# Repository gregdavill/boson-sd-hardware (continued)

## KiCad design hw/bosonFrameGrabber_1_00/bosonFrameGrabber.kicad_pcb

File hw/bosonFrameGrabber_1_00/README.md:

# bosonFrameGrabber v1.00

	Board Status: Discarded
	Note: bad footprint for HyperRam.

A Small FPGA based board. Designed to connect to a FLIR Boson Camera, and save images from the camera to a microSD card.

## Hardware

* ICE40HX8K in csBGA132 package
* HyperRAM: high density, but low pin count.
* QSPI Memory
* MicroSD socket
* MEMs Oscillator
* JST GH SM06 locking Data/Power connector
* JTAG exposed via pogo pin pads.
* 2x 5V tolerant I/Os on connector
* 1x LED!

Prototype Limitations:
* Not quite enough decoupling, not too close to BGA pads.
* 3.3V only! (Integrated LDOs handle FPGA rails, but input power is connected directly to the Boson)
* Non-ideal BGA footprint to reduce prototyping costs.

## Goals

I have not worked with FPGAs in a project before, This project is a toy project of mine, to learn while having a clear goal. 

* Use Icestorm toolchain to develop for FPGA
* Deploy a risc-V softcore into the HX8K.
* Develop a HyperRAM interface.
* Develop/Integrate SDMMC IP. (Intially SD in SPI mode)
* Save Images from the CMOS camera interface to the SD card.

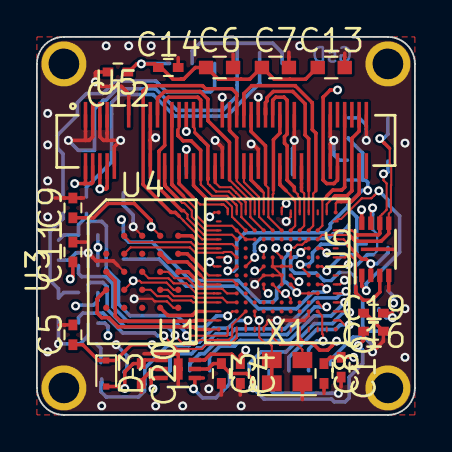
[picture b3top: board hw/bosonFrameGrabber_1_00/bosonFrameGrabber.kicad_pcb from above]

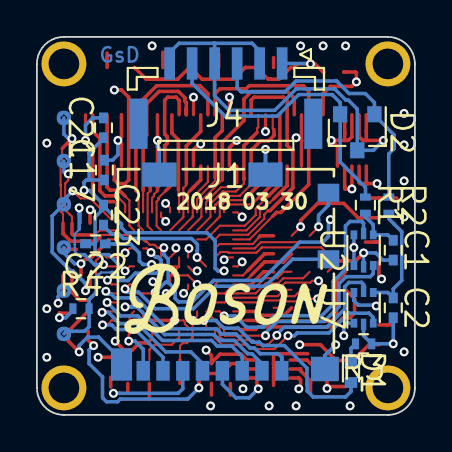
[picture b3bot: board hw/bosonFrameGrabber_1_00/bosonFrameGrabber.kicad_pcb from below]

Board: 4 copper layers, 21.0 x 21.0 mm, 38 parts (16 on the bottom side), 68 nets.

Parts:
C1, C2: 100pF; C_0402
C3, C4: 1uF; C_0402
C5: 100nF; C_0402
C6, C7, C13: 10uF; C_0603
C8, C9, C10, C11, C12, C14, C16, C17, C19, C20, C21, C22, C23: 100n; C_0402
D1: LED; LED_0402
D2: D_TVS_x2_AAC; SOT-23
D3: D_ALT; D_SC-80
J1: JST GH Series; JST_GH_BM06B-GHS-TBT_06x1.25mm_Straight
J4: MicroSD; 1040310811
R1, R2: 100R; R_0402
R3: R; R_0402
R4: 10k; R_0402
U1: MIC5370; DFN-6-1EP_2x2mm_Pitch0.5mm
U2, U7: SN74LVC1T45; SOT-666
U3: ICE40HX8K; csBGA_132
U4: S27KS0641; BGA_24
U5: Boson; DF40_80Pin
U6: AT25SF081; DFN-8-1EP_3x2mm_Pitch0.5mm
X1: ASDMB; Oscillator_SMD_SeikoEpson_SG210-4pin_2.5x2.0mm

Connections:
16MHZ_IN: U3.G1, X1.3
+1V2: C3.1, C17.1, C19.1, C21.1, C22.2, C23.1, U1.5, U3.C8, U3.F8, U3.G6, U3.H9, U3.J4, U3.J7, U3.M8
+1V8: C4.1, C8.1, C9.1, C10.1, C11.1, U1.6, U3.A8, U3.F6, U3.F9, U3.H14, U4.B4, U4.D1, U4.E4
+2V5: C5.1, D3.1, U3.A14
+3V3: C6.1, C7.1, C12.1, C13.1, C14.1, C16.1, C20.1, D3.2, J1.1, J4.4, R4.1, U1.1, U1.3, U1.4, U2.1, U2.6, U3.E3, U3.J6, U3.J9, U3.K1, U3.L5, U3.L11, U3.M5, U5.2, U5.4, U5.6, U5.8, U6.8, U7.1, U7.6, X1.1, X1.4
BOSON_CK: U3.G14, U5.55
BOSON_DATA0: U3.N14, U5.77
BOSON_DATA1: U3.K12, U5.62
BOSON_DATA2: U3.L14, U5.51
BOSON_DATA3: U3.J12, U5.56
BOSON_DATA4: U3.C14, U5.27
BOSON_DATA5: U3.B14, U5.28
BOSON_DATA6: U3.D12, U5.32
BOSON_DATA7: U3.E12, U5.31
BOSON_DATA8: U3.C12, U3.D11, U3.E11, U5.25
BOSON_DATA9: U3.G12, U5.46
BOSON_DATA10: U3.L12, U5.45
BOSON_DATA11: U3.F14, U5.48
BOSON_DATA12: U3.H12, U5.47
BOSON_DATA13: U3.E14, U5.41
BOSON_DATA14: U3.F12, U5.21
BOSON_DATA15: U3.D14, U5.38
BOSON_DATA_EN: U3.P14, U5.78
BOSON_HSYNC: U3.M12, U5.73
BOSON_RESET: U3.A12, U5.24
BOSON_RXD: U3.C11, U5.33
BOSON_TXD: U3.A11, U5.43
BOSON_VSYNC: U3.K14, U5.53
FPGA_RESET: R4.2, U3.L10
GND: C1.2, C2.2, C3.2, C4.2, C5.2, C6.2, C7.2, C8.2, C9.2, C10.2, C11.2, C12.2, C13.2, C14.2, C16.2, C17.2, C19.2, C20.2, C21.2, D2.3, J1.2, J1.4, J1.6, J4.6, J4.9, J4.11, R3.1, U1.2, U1.7, U2.2, U3.A9, U3.F1, U3.F7, U3.G7, U3.G8, U3.G9, U3.H6, U3.H7, U3.H8, U3.J8, U3.J14, U3.L3, U3.P6, U4.B3, U4.C1, U4.E5, U5.1, U5.3, U5.5, U5.7, U5.10, U5.13, U5.19, U5.20, U5.29, U5.30, U5.39, U5.40, U5.49, U5.50, U5.59, U5.60, U5.69, U5.70, U5.79, U6.4, U6.9, U7.2, X1.2
HYPERBUS_CK: U3.C9, U4.B2
HYPERBUS_CK#: U3.A10, U4.B1
HYPERBUS_CS#: U3.A2, U4.A3
HYPERBUS_DQ0: U3.C5, U4.D3
HYPERBUS_DQ1: U3.C6, U4.D2
HYPERBUS_DQ2: U3.A4, U4.C4
HYPERBUS_DQ3: U3.C4, U4.D4
HYPERBUS_DQ4: U3.A3, U4.D5
HYPERBUS_DQ5: U3.A6, U4.E3
HYPERBUS_DQ6: U3.A7, U4.E2
HYPERBUS_DQ7: U3.C10, U4.E1
HYPERBUS_RESET#: U3.A1, U4.A4
HYPERBUS_RWDS: U3.A5, U4.C3
IO_A: D2.2, J1.5, R1.1
IO_A_DIR: U2.5, U3.C3
IO_A_INTERNAL: U2.3, U3.B1
IO_B: D2.1, J1.3, R2.1
IO_B_DIR: U3.D3, U7.5
IO_B_INTERNAL: U3.C1, U7.3
LED_A: D1.2, U3.D1
unnamed: C1.1, R1.2, U2.4
unnamed: C2.1, R2.2, U7.4
unnamed: C22.1, U3.L7
unnamed: C23.2, U3.D8
unnamed: D1.1, R3.2
QSPI_D2: U3.P9, U6.3
QSPI_D3: U3.P8, U6.7
SD_CD: J4.10, U3.M6
SD_CK: J4.5, U3.P3
SD_CMD: J4.3, U3.P4
SD_DAT0: J4.7, U3.P2
SD_DAT1: J4.8, U3.M3
SD_DAT2: J4.1, U3.P5
SD_DAT3: J4.2, U3.M4
SPI_CONFIG_MISO: U3.P11, U6.2
SPI_CONFIG_MOSI: U3.M11, U6.5
SPI_CONFIG_SCK: U3.P12, U6.6
SPI_CONFIG_SS: U3.P13, U6.1

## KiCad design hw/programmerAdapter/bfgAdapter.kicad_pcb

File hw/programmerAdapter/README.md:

# programmerAdapter

	Project Stage: Early Development

A simple adapter for Esden's ftdi universial Breakout board. <br>https://github.com/icebreaker-fpga/icebreaker/tree/master/hardware/ftdi-v1.0a 

## Design
Designed to suit the BosonFrameGrabber PCB. This design uses pogoPins to make connection and screws over the mounting holes into the Boson.

## Licence 

To match Esden's work this PCB is licenced: CC-BY-SA

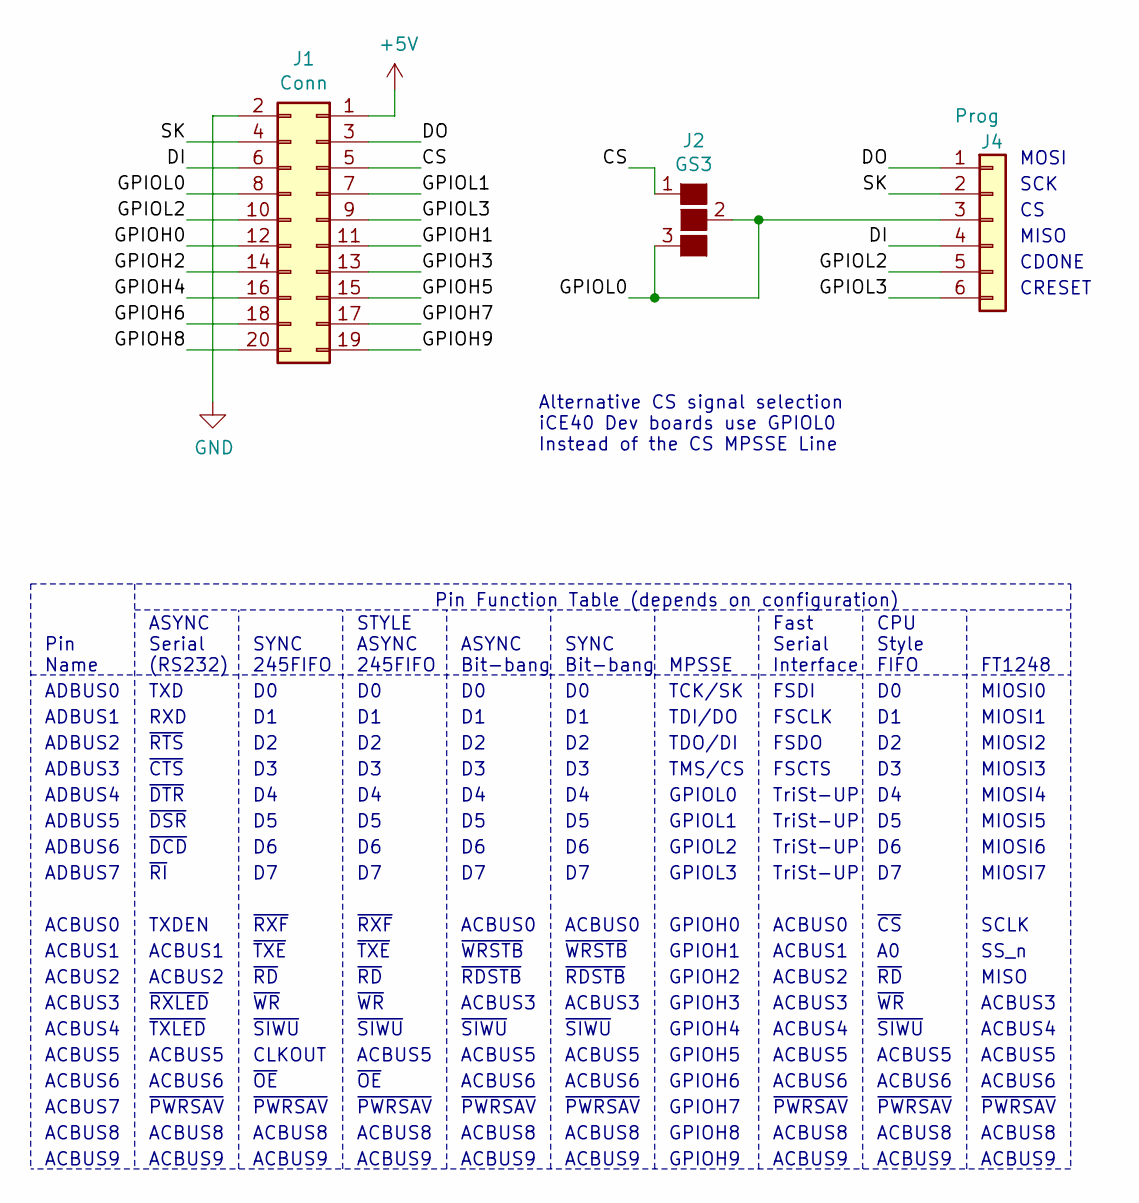
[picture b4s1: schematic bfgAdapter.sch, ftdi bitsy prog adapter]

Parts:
J1: Conn; FTSH-EDGE-20pin
J2: GS3
J4: Prog; PinSocket_1x06_P2.54mm_Vertical

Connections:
+5V: J1.1
/CS: J1.5, J2.1 (G1)
/DI: J1.6, J4.4
/DO: J1.3, J4.1
/GPIOH0: J1.12
/GPIOH1: J1.11
/GPIOH2: J1.14
/GPIOH3: J1.13
/GPIOH4: J1.16
/GPIOH5: J1.15
/GPIOH6: J1.18
/GPIOH7: J1.17
/GPIOH8: J1.20
/GPIOH9: J1.19
/GPIOL0: J1.8, J2.2 (G2), J2.3 (G3), J4.3
/GPIOL1: J1.7
/GPIOL2: J1.10, J4.5
/GPIOL3: J1.9, J4.6
/SK: J1.4, J4.2
GND: J1.2

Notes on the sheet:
STYLE ASYNC 245FIFO
~RXF
~TXE
~RD
~WR
~SIWU
ACBUS5
~OE
~PWRSAV
ACBUS8
ACBUS9
ASYNC Bit-bang
ACBUS0
~WRSTB
~RDSTB
ACBUS3
ACBUS6
SYNC Bit-bang
MPSSE
TCK/SK
TDI/DO
TDO/DI
TMS/CS
GPIOL0
GPIOL1
GPIOL2
GPIOL3
GPIOH0
GPIOH1
GPIOH2
GPIOH3
GPIOH4
GPIOH5
GPIOH6
GPIOH7
GPIOH8
GPIOH9
Fast Serial Interface
FSDI
FSCLK

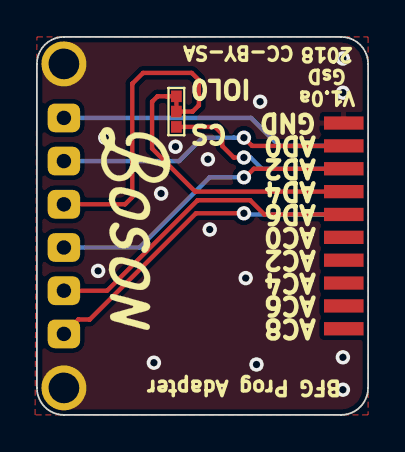
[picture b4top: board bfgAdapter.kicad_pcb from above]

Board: 2 copper layers, 18.4 x 21.0 mm, 3 parts (1 on the bottom side), 7 nets.

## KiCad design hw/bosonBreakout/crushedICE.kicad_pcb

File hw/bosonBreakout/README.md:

# bosonBreakout

	Project Stage: VERY Early Development
	!!! Note this design has an incorrect HyperRam footprint !!!

(Initially a project called: CrushedICE)

A FPGA based camera interface board. This PCB was developed before the bosonFrameGrabber, and has a vastly different architecture. It uses an ICE5LP4K, HyperRAM and a QSPI bridge to a SAMD51.

FPGA+RAM will act as a FIFO, connect to SAMD51 via QSPI. To read out a frame when required. SAMD51 has a SDMMC module so it handles the writing to an SD card. 

Filled with test headers to make it easy to connect to a Saleae Logic analyser.

## Hardware

* ICE5LP4K in QFN48 package
* HyperRAM: high density, but low pin count.
* QSPI Bus
* Microchip SAMD51
* MicroSD socket
* 16MHz Oscillator
* 6x LEDs!
* TOO MANY TEST POINTS!

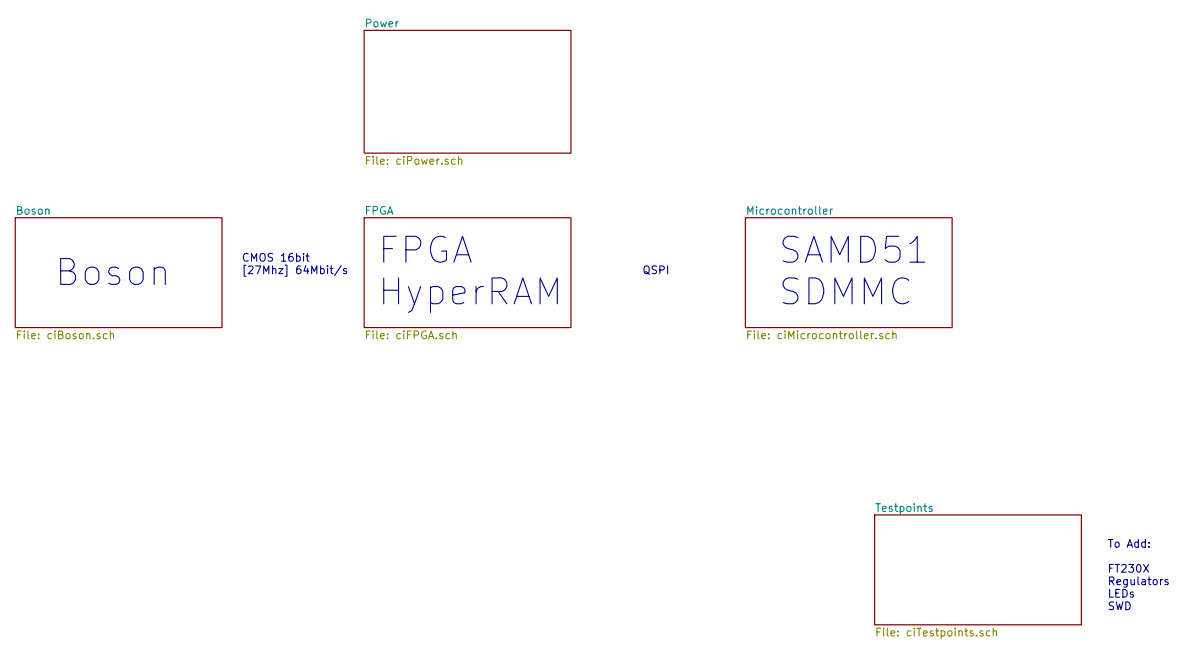
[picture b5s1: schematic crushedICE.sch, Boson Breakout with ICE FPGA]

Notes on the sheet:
To Add: FT230X Regulators LEDs SWD
Boson
FPGA HyperRAM
CMOS 16bit [27Mhz] 64Mbit/s
QSPI
SAMD51 SDMMC

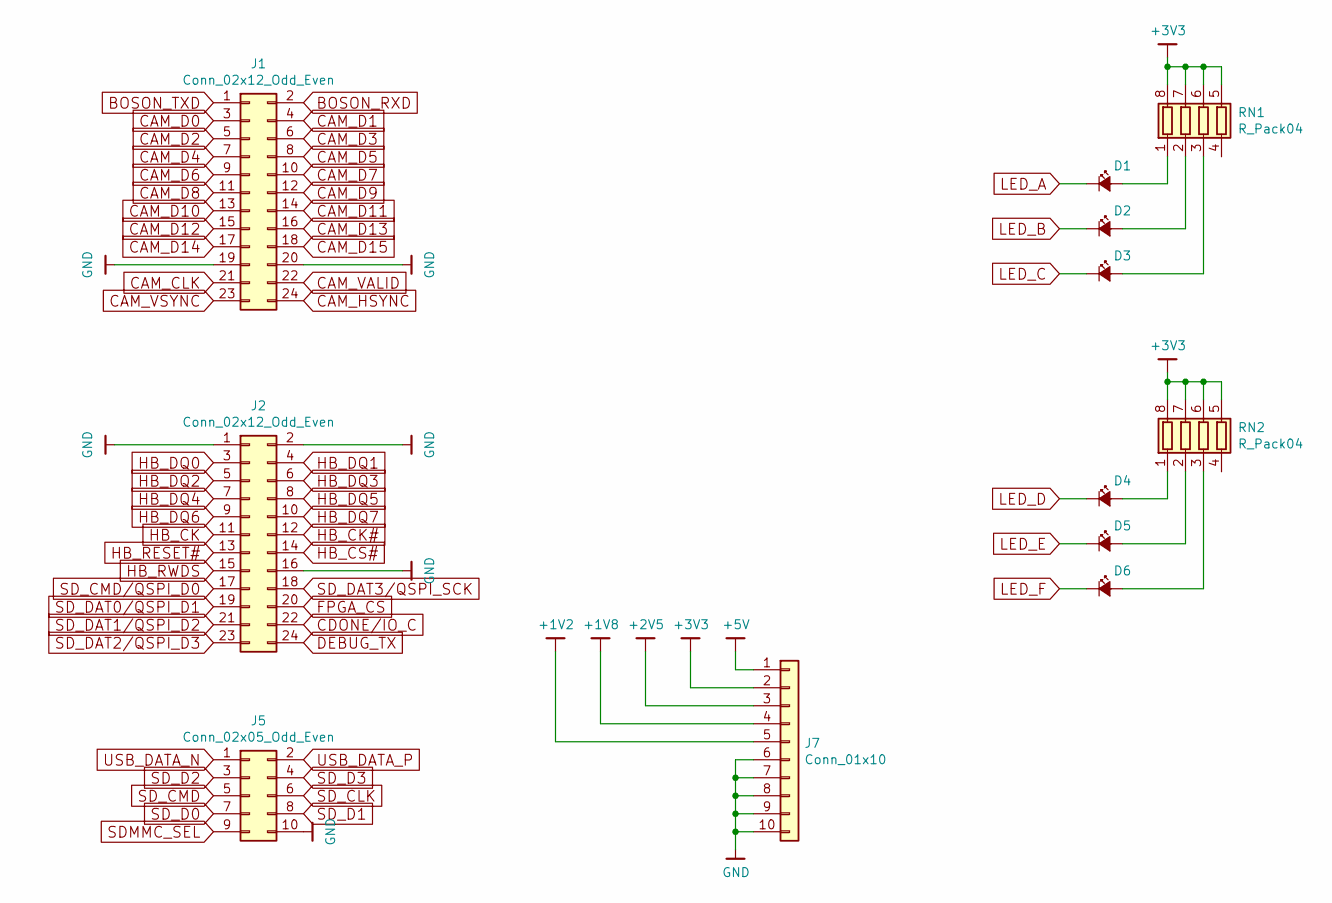
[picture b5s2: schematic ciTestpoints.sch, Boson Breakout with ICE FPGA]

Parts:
D1, D2, D3, D4, D5, D6: led green; LED_0805
J1, J2: Conn_02x12_Odd_Even
J5: Conn_02x05_Odd_Even; Pin_Header_Straight_2x05_Pitch2.54mm
J7: Conn_01x10; Pin_Header_Straight_1x10_Pitch2.54mm
RN1, RN2: R_Pack04; R_Array_Convex_4x0603

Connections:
+1V2: J7.5; also elsewhere on the board
+1V8: J7.4; also elsewhere on the board
+2V5: J7.3; also elsewhere on the board
+3V3: J7.2, RN1.5 (R4.2), RN1.6 (R3.2), RN1.7 (R2.2), RN1.8 (R1.2), RN2.5 (R4.2), RN2.6 (R3.2), RN2.7 (R2.2), RN2.8 (R1.2); also elsewhere on the board
+5V: J7.1; also elsewhere on the board
BOSON_RXD: J1.2; also elsewhere on the board
BOSON_TXD: J1.1; also elsewhere on the board
CAM_CLK: J1.21; also elsewhere on the board
CAM_D0: J1.3; also elsewhere on the board
CAM_D1: J1.4; also elsewhere on the board
CAM_D2: J1.5; also elsewhere on the board
CAM_D3: J1.6; also elsewhere on the board
CAM_D4: J1.7; also elsewhere on the board
CAM_D5: J1.8; also elsewhere on the board
CAM_D6: J1.9; also elsewhere on the board
CAM_D7: J1.10; also elsewhere on the board
CAM_D8: J1.11; also elsewhere on the board
CAM_D9: J1.12; also elsewhere on the board
CAM_D10: J1.13; also elsewhere on the board
CAM_D11: J1.14; also elsewhere on the board
CAM_D12: J1.15; also elsewhere on the board
CAM_D13: J1.16; also elsewhere on the board
CAM_D14: J1.17; also elsewhere on the board
CAM_D15: J1.18; also elsewhere on the board
CAM_HSYNC: J1.24; also elsewhere on the board
CAM_VALID: J1.22; also elsewhere on the board
CAM_VSYNC: J1.23; also elsewhere on the board
CDONE/IO_C: J2.22; also elsewhere on the board
DEBUG_TX: J2.24; also elsewhere on the board
FPGA_CS: J2.20; also elsewhere on the board
GND: J1.19, J1.20, J2.1, J2.2, J2.16, J5.10, J7.6, J7.7, J7.8, J7.9, J7.10; also elsewhere on the board
HB_CK: J2.11; also elsewhere on the board
HB_CK#: J2.12; also elsewhere on the board
HB_CS#: J2.14; also elsewhere on the board
HB_DQ0: J2.3; also elsewhere on the board
HB_DQ1: J2.4; also elsewhere on the board
HB_DQ2: J2.5; also elsewhere on the board
HB_DQ3: J2.6; also elsewhere on the board
HB_DQ4: J2.7; also elsewhere on the board
HB_DQ5: J2.8; also elsewhere on the board
HB_DQ6: J2.9; also elsewhere on the board
HB_DQ7: J2.10; also elsewhere on the board
HB_RESET#: J2.13; also elsewhere on the board
HB_RWDS: J2.15; also elsewhere on the board
LED_A: D1.1 (K); also elsewhere on the board
LED_B: D2.1 (K); also elsewhere on the board
LED_C: D3.1 (K); also elsewhere on the board
LED_D: D4.1 (K); also elsewhere on the board
LED_E: D5.1 (K); also elsewhere on the board
LED_F: D6.1 (K); also elsewhere on the board
unnamed: D1.2 (A), RN1.1 (R1.1)
unnamed: D2.2 (A), RN1.2 (R2.1)
unnamed: D3.2 (A), RN1.3 (R3.1)
unnamed: D4.2 (A), RN2.1 (R1.1)
unnamed: D5.2 (A), RN2.2 (R2.1)
unnamed: D6.2 (A), RN2.3 (R3.1)
SDMMC_SEL: J5.9; also elsewhere on the board
SD_CLK: J5.6; also elsewhere on the board
SD_CMD: J5.5; also elsewhere on the board
SD_CMD/QSPI_D0: J2.17; also elsewhere on the board
SD_D0: J5.7; also elsewhere on the board
SD_D1: J5.8; also elsewhere on the board
SD_D2: J5.3; also elsewhere on the board
SD_D3: J5.4; also elsewhere on the board
SD_DAT0/QSPI_D1: J2.19; also elsewhere on the board
SD_DAT1/QSPI_D2: J2.21; also elsewhere on the board
SD_DAT2/QSPI_D3: J2.23; also elsewhere on the board
SD_DAT3/QSPI_SCK: J2.18; also elsewhere on the board
USB_DATA_N: J5.1; also elsewhere on the board
USB_DATA_P: J5.2; also elsewhere on the board

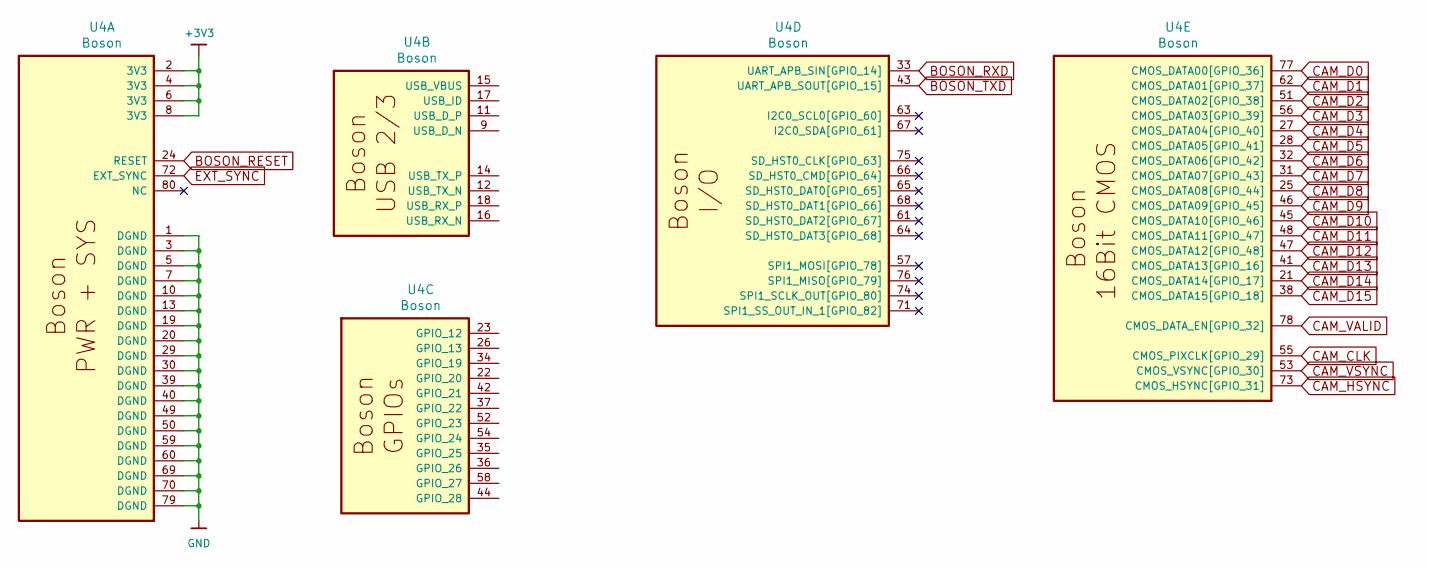
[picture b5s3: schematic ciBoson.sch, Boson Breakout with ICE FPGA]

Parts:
U4: Boson; DF40_80Pin

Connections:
+3V3: U4.2 (3V3), U4.4 (3V3), U4.6 (3V3), U4.8 (3V3); also elsewhere on the board
BOSON_RESET: U4.24 (RESET)
BOSON_RXD: U4.33 (UART_APB_SIN[GPIO_14]); also elsewhere on the board
BOSON_TXD: U4.43 (UART_APB_SOUT[GPIO_15]); also elsewhere on the board
CAM_CLK: U4.55 (CMOS_PIXCLK[GPIO_29]); also elsewhere on the board
CAM_D0: U4.77 (CMOS_DATA00[GPIO_36]); also elsewhere on the board
CAM_D1: U4.62 (CMOS_DATA01[GPIO_37]); also elsewhere on the board
CAM_D2: U4.51 (CMOS_DATA02[GPIO_38]); also elsewhere on the board
CAM_D3: U4.56 (CMOS_DATA03[GPIO_39]); also elsewhere on the board
CAM_D4: U4.27 (CMOS_DATA04[GPIO_40]); also elsewhere on the board
CAM_D5: U4.28 (CMOS_DATA05[GPIO_41]); also elsewhere on the board
CAM_D6: U4.32 (CMOS_DATA06[GPIO_42]); also elsewhere on the board
CAM_D7: U4.31 (CMOS_DATA07[GPIO_43]); also elsewhere on the board
CAM_D8: U4.25 (CMOS_DATA08[GPIO_44]); also elsewhere on the board
CAM_D9: U4.46 (CMOS_DATA09[GPIO_45]); also elsewhere on the board
CAM_D10: U4.45 (CMOS_DATA10[GPIO_46]); also elsewhere on the board
CAM_D11: U4.48 (CMOS_DATA11[GPIO_47]); also elsewhere on the board
CAM_D12: U4.47 (CMOS_DATA12[GPIO_48]); also elsewhere on the board
CAM_D13: U4.41 (CMOS_DATA13[GPIO_16]); also elsewhere on the board
CAM_D14: U4.21 (CMOS_DATA14[GPIO_17]); also elsewhere on the board
CAM_D15: U4.38 (CMOS_DATA15[GPIO_18]); also elsewhere on the board
CAM_HSYNC: U4.73 (CMOS_HSYNC[GPIO_31]); also elsewhere on the board
CAM_VALID: U4.78 (CMOS_DATA_EN[GPIO_32]); also elsewhere on the board
CAM_VSYNC: U4.53 (CMOS_VSYNC[GPIO_30]); also elsewhere on the board
EXT_SYNC: U4.72 (EXT_SYNC)
GND: U4.1 (DGND), U4.3 (DGND), U4.5 (DGND), U4.7 (DGND), U4.10 (DGND), U4.13 (DGND), U4.19 (DGND), U4.20 (DGND), U4.29 (DGND), U4.30 (DGND), U4.39 (DGND), U4.40 (DGND), U4.49 (DGND), U4.50 (DGND), U4.59 (DGND), U4.60 (DGND), U4.69 (DGND), U4.70 (DGND), U4.79 (DGND); also elsewhere on the board

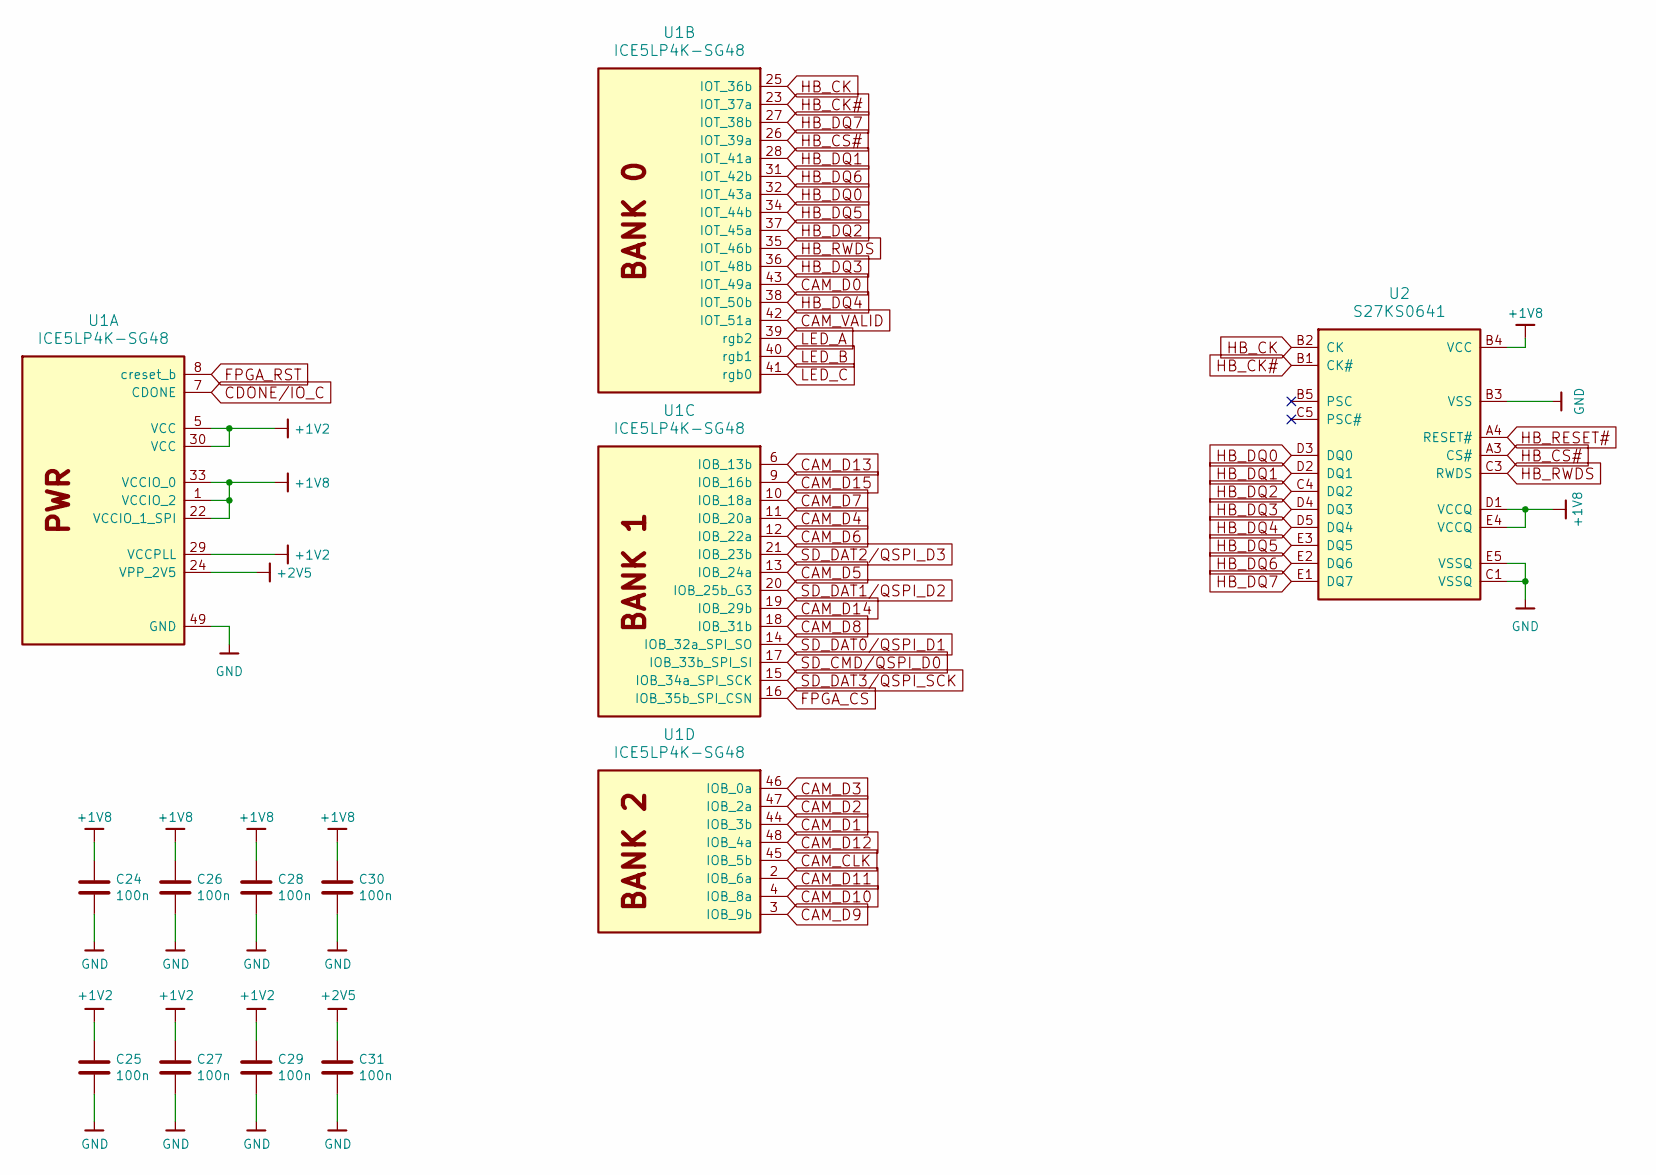
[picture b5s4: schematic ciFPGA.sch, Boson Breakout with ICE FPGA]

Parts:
C24, C25, C26, C27, C28, C29, C30, C31: 100n; C_0603
U1: ICE5LP4K-SG48; QFN-48-1EP_7x7mm_Pitch0.5mm
U2: S27KS0641; BGA_24

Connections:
+1V2: C25.1, C27.1, C29.1, U1.5 (VCC), U1.29 (VCCPLL), U1.30 (VCC); also elsewhere on the board
+1V8: C24.1, C26.1, C28.1, C30.1, U1.1 (VCCIO_2), U1.22 (VCCIO_1_SPI), U1.33 (VCCIO_0), U2.B4 (VCC), U2.D1 (VCCQ), U2.E4 (VCCQ); also elsewhere on the board
+2V5: C31.1, U1.24 (VPP_2V5); also elsewhere on the board
CAM_CLK: U1.45 (IOB_5b); also elsewhere on the board
CAM_D0: U1.43 (IOT_49a); also elsewhere on the board
CAM_D1: U1.44 (IOB_3b); also elsewhere on the board
CAM_D2: U1.47 (IOB_2a); also elsewhere on the board
CAM_D3: U1.46 (IOB_0a); also elsewhere on the board
CAM_D4: U1.11 (IOB_20a); also elsewhere on the board
CAM_D5: U1.13 (IOB_24a); also elsewhere on the board
CAM_D6: U1.12 (IOB_22a); also elsewhere on the board
CAM_D7: U1.10 (IOB_18a); also elsewhere on the board
CAM_D8: U1.18 (IOB_31b); also elsewhere on the board
CAM_D9: U1.3 (IOB_9b); also elsewhere on the board
CAM_D10: U1.4 (IOB_8a); also elsewhere on the board
CAM_D11: U1.2 (IOB_6a); also elsewhere on the board
CAM_D12: U1.48 (IOB_4a); also elsewhere on the board
CAM_D13: U1.6 (IOB_13b); also elsewhere on the board
CAM_D14: U1.19 (IOB_29b); also elsewhere on the board
CAM_D15: U1.9 (IOB_16b); also elsewhere on the board
CAM_VALID: U1.42 (IOT_51a); also elsewhere on the board
CDONE/IO_C: U1.7 (CDONE); also elsewhere on the board
FPGA_CS: U1.16 (IOB_35b_SPI_CSN); also elsewhere on the board
FPGA_RST: U1.8 (creset_b); also elsewhere on the board
GND: C24.2, C25.2, C26.2, C27.2, C28.2, C29.2, C30.2, C31.2, U1.49 (GND), U2.B3 (VSS), U2.C1 (VSSQ), U2.E5 (VSSQ); also elsewhere on the board
HB_CK: U1.25 (IOT_36b), U2.B2 (CK); also elsewhere on the board
HB_CK#: U1.23 (IOT_37a), U2.B1 (CK#); also elsewhere on the board
HB_CS#: U1.26 (IOT_39a), U2.A3 (CS#); also elsewhere on the board
HB_DQ0: U1.32 (IOT_43a), U2.D3 (DQ0); also elsewhere on the board
HB_DQ1: U1.28 (IOT_41a), U2.D2 (DQ1); also elsewhere on the board
HB_DQ2: U1.37 (IOT_45a), U2.C4 (DQ2); also elsewhere on the board
HB_DQ3: U1.36 (IOT_48b), U2.D4 (DQ3); also elsewhere on the board
HB_DQ4: U1.38 (IOT_50b), U2.D5 (DQ4); also elsewhere on the board
HB_DQ5: U1.34 (IOT_44b), U2.E3 (DQ5); also elsewhere on the board
HB_DQ6: U1.31 (IOT_42b), U2.E2 (DQ6); also elsewhere on the board
HB_DQ7: U1.27 (IOT_38b), U2.E1 (DQ7); also elsewhere on the board
HB_RESET#: U2.A4 (RESET#); also elsewhere on the board
HB_RWDS: U1.35 (IOT_46b), U2.C3 (RWDS); also elsewhere on the board
LED_A: U1.39 (rgb2); also elsewhere on the board
LED_B: U1.40 (rgb1); also elsewhere on the board
LED_C: U1.41 (rgb0); also elsewhere on the board
SD_CMD/QSPI_D0: U1.17 (IOB_33b_SPI_SI); also elsewhere on the board
SD_DAT0/QSPI_D1: U1.14 (IOB_32a_SPI_SO); also elsewhere on the board
SD_DAT1/QSPI_D2: U1.20 (IOB_25b_G3); also elsewhere on the board
SD_DAT2/QSPI_D3: U1.21 (IOB_23b); also elsewhere on the board
SD_DAT3/QSPI_SCK: U1.15 (IOB_34a_SPI_SCK); also elsewhere on the board

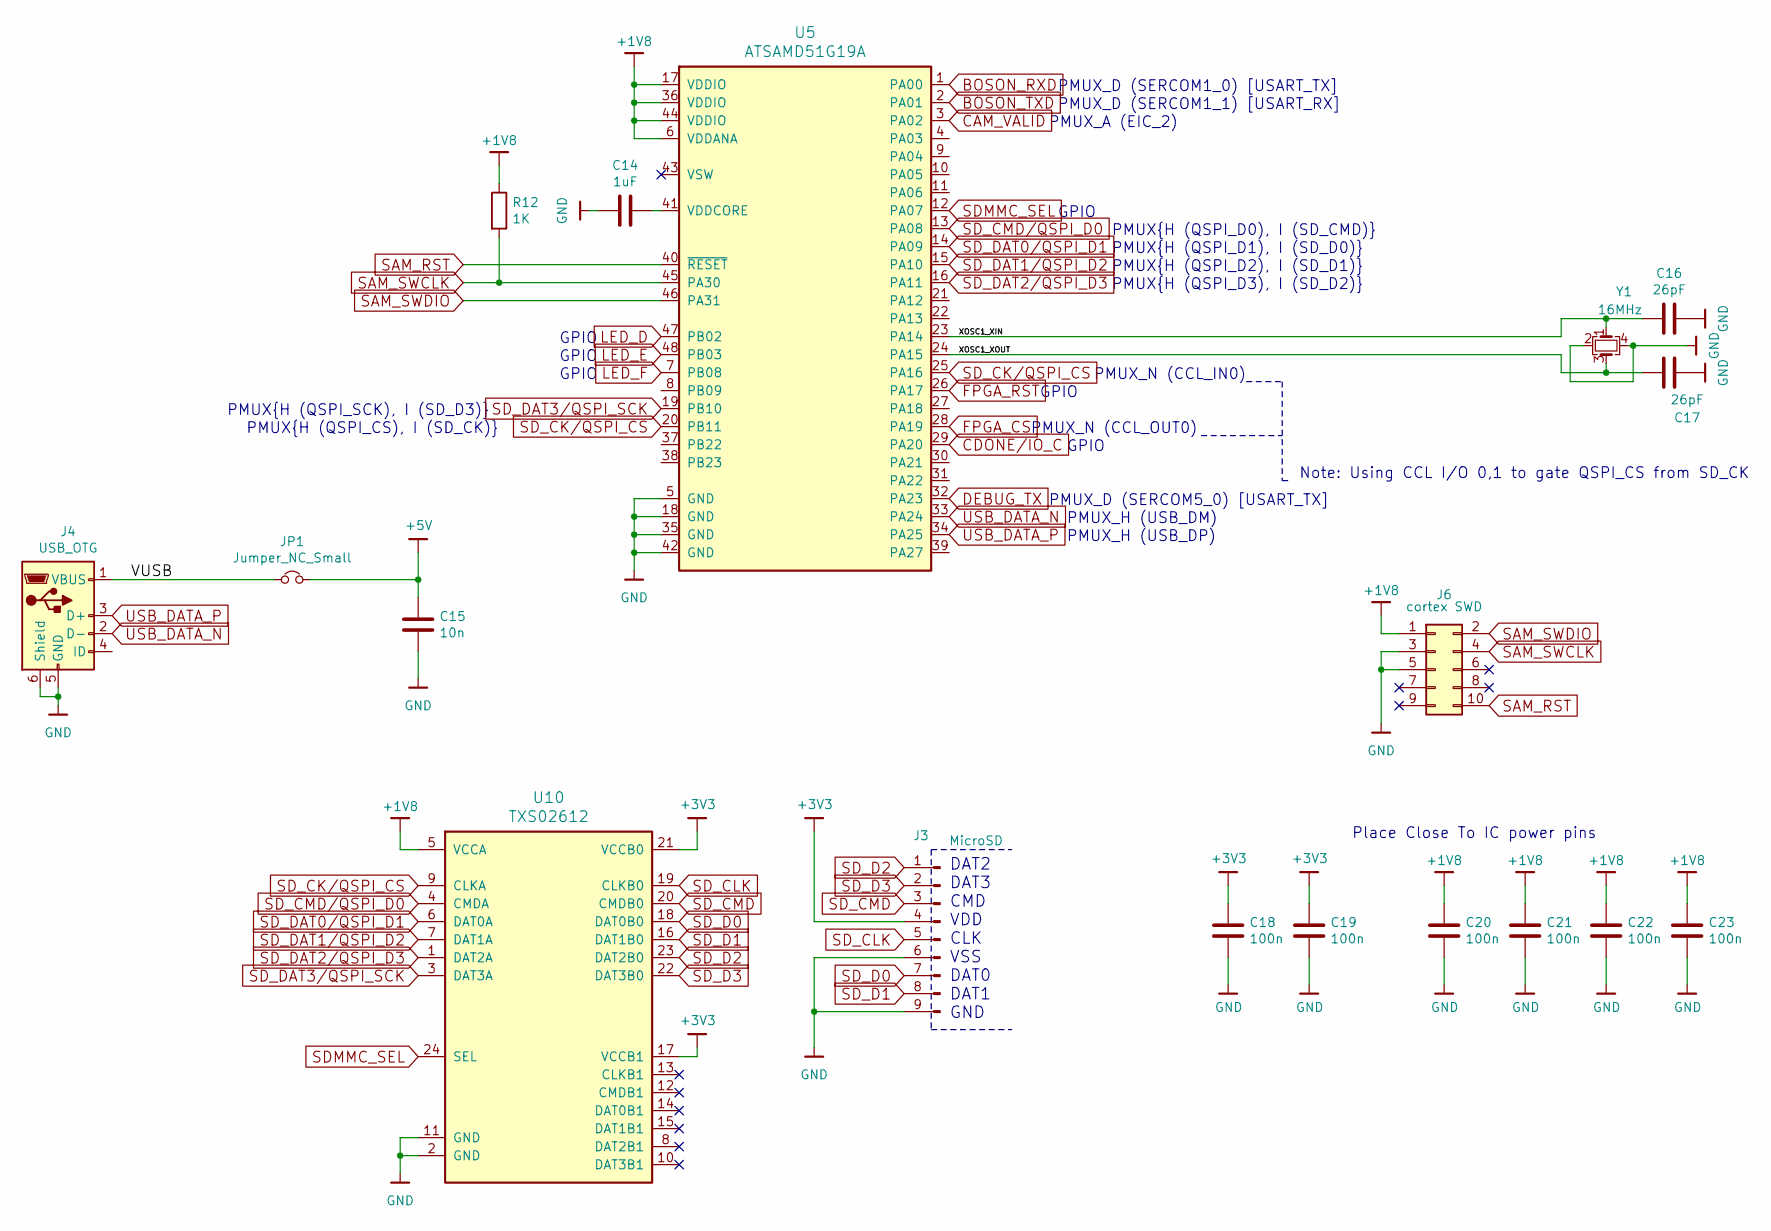
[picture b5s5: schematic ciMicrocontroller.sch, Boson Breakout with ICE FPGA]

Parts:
C14: 1uF; C_0603
C15: 10n; C_0603
C16, C17: 26pF; C_0603
C18, C19, C20, C21, C22, C23: 100n; C_0603
J3: MicroSD; SD_holder_472190001
J4: USB_OTG; USB_Micro-B_10103594-0001LF
J6: cortex SWD; CORTEX_SWD
JP1: Jumper_NC_Small; R_0201_NoSilk
R12: 1K; R_0603
U5: ATSAMD51G19A; QFN-48-1EP_7x7mm_Pitch0.5mm
U10: TXS02612; QFN-24-1EP_4x4mm_Pitch0.5mm
Y1: 16MHz; Crystal_SMD_3225-4pin_3.2x2.5mm

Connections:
+1V8: C20.1, C21.1, C22.1, C23.1, J6.1, R12.1, U5.6 (VDDANA~), U5.17 (VDDIO~), U5.36 (VDDIO~), U5.44 (VDDIO~), U10.5 (VCCA); also elsewhere on the board
+3V3: C18.1, C19.1, J3.4, U10.17 (VCCB1), U10.21 (VCCB0); also elsewhere on the board
+5V: C15.1, JP1.2; also elsewhere on the board
/Microcontroller/VUSB: J4.1 (VBUS), JP1.1
/Microcontroller/XOSC1_XIN: C16.2, U5.23 (PA14~), Y1.1
/Microcontroller/XOSC1_XOUT: C17.2, U5.24 (PA15~), Y1.3
BOSON_RXD: U5.1 (PA00); also elsewhere on the board
BOSON_TXD: U5.2 (PA01~); also elsewhere on the board
CAM_VALID: U5.3 (PA02~); also elsewhere on the board
CDONE/IO_C: U5.29 (PA20~); also elsewhere on the board
DEBUG_TX: U5.32 (PA23~); also elsewhere on the board
FPGA_CS: U5.28 (PA19~); also elsewhere on the board
FPGA_RST: U5.26 (PA17~); also elsewhere on the board
GND: C14.2, C15.2, C16.1, C17.1, C18.2, C19.2, C20.2, C21.2, C22.2, C23.2, J3.6, J3.9, J4.5 (GND), J4.6 (Shield), J6.3, J6.5, U5.5 (GND~), U5.18 (GND~), U5.35 (GND~), U5.42 (GND), U5.49 (GND), U10.2 (GND), U10.11 (GND), Y1.2, Y1.4; also elsewhere on the board
LED_D: U5.47 (PB02~); also elsewhere on the board
LED_E: U5.48 (PB03~); also elsewhere on the board
LED_F: U5.7 (PB08~); also elsewhere on the board
unnamed: C14.1, U5.41 (VDDCORE~)
SAM_RST: J6.10, U5.40 (~RESET)
SAM_SWCLK: J6.4, R12.2, U5.45 (PA30~)
SAM_SWDIO: J6.2, U5.46 (PA31~)
SDMMC_SEL: U5.12 (PA07~), U10.24 (SEL); also elsewhere on the board
SD_CK/QSPI_CS: U5.20 (PB11~), U5.25 (PA16~), U10.9 (CLKA)
SD_CLK: J3.5, U10.19 (CLKB0); also elsewhere on the board
SD_CMD: J3.3, U10.20 (CMDB0); also elsewhere on the board
SD_CMD/QSPI_D0: U5.13 (PA08~), U10.4 (CMDA); also elsewhere on the board
SD_D0: J3.7, U10.18 (DAT0B0); also elsewhere on the board
SD_D1: J3.8, U10.16 (DAT1B0); also elsewhere on the board
SD_D2: J3.1, U10.23 (DAT2B0); also elsewhere on the board
SD_D3: J3.2, U10.22 (DAT3B0); also elsewhere on the board
SD_DAT0/QSPI_D1: U5.14 (PA09~), U10.6 (DAT0A); also elsewhere on the board
SD_DAT1/QSPI_D2: U5.15 (PA10~), U10.7 (DAT1A); also elsewhere on the board
SD_DAT2/QSPI_D3: U5.16 (PA11~), U10.1 (DAT2A); also elsewhere on the board
SD_DAT3/QSPI_SCK: U5.19 (PB10~), U10.3 (DAT3A); also elsewhere on the board
USB_DATA_N: J4.2 (D-), U5.33 (PA24~); also elsewhere on the board
USB_DATA_P: J4.3 (D+), U5.34 (PA25~); also elsewhere on the board

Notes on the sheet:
DAT2 DAT3 CMD VDD CLK VSS DAT0 DAT1 GND
PMUX_A (EIC_2)
PMUX_D (SERCOM1_0) [USART_TX]
PMUX_D (SERCOM1_1) [USART_RX]
PMUX_N (CCL_IN0)
PMUX_N (CCL_OUT0)
GPIO
PMUX_H (USB_DM)
PMUX_H (USB_DP)
PMUX{H (QSPI_D0), I (SD_CMD)}
PMUX{H (QSPI_D1), I (SD_D0)}
PMUX{H (QSPI_D2), I (SD_D1)}
PMUX{H (QSPI_D3), I (SD_D2)}
PMUX{H (QSPI_SCK), I (SD_D3)}
PMUX{H (QSPI_CS), I (SD_CK)}
Note: Using CCL I/O 0,1 to gate QSPI_CS from SD_CK
PMUX_D (SERCOM5_0) [USART_TX]
Place Close To IC power pins

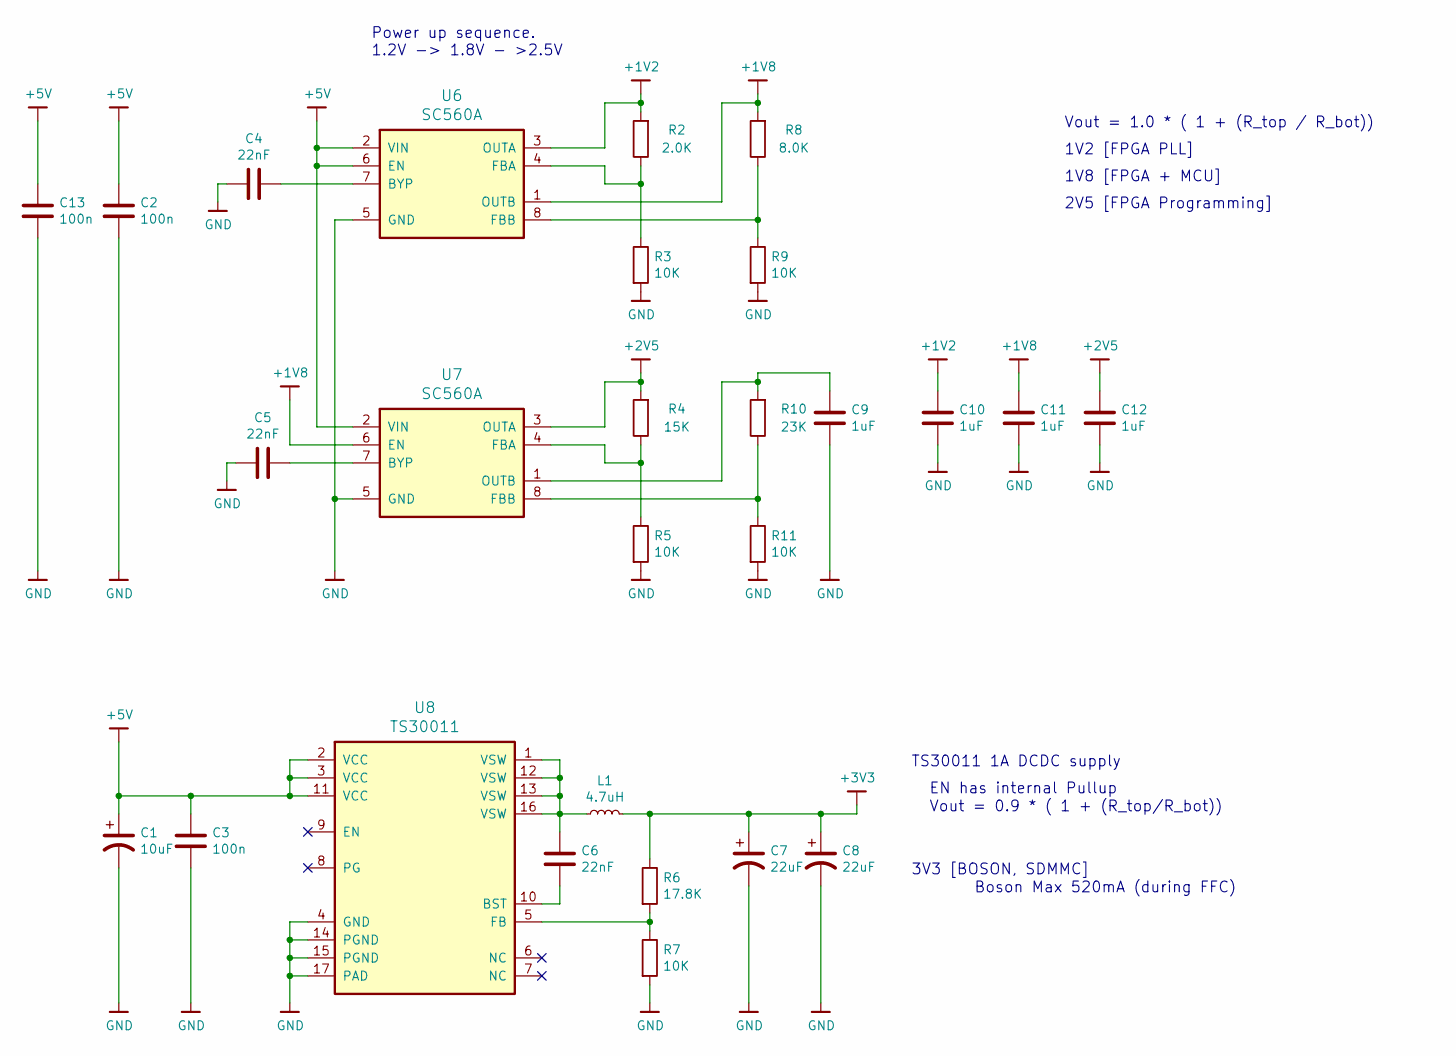
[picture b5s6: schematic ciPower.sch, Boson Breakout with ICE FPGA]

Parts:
C1: 10uF; C_0805
C2, C3, C13: 100n; C_0603
C4, C5, C6: 22nF; C_0603
C7, C8: 22uF; C_0805
C9, C10, C11, C12: 1uF; C_0603
L1: 4.7uH; Inductor_Taiyo-Yuden_MD-3030
R2: 2.0K; R_0603
R3, R5, R7, R9, R11: 10K; R_0603
R4: 15K; R_0603
R6: 17.8K; R_0603
R8: 8.0K; R_0603
R10: 23K; R_0603
U6, U7: SC560A; MLPQ-UT8
U8: TS30011; QFN-16-1EP_3x3mm_Pitch0.5mm_ThermalVias

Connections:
+1V2: C10.1, R2.2, U6.3 (OUTA); also elsewhere on the board
+1V8: C11.1, R8.2, U6.1 (OUTB), U7.6 (EN); also elsewhere on the board
+2V5: C12.1, R4.2, U7.3 (OUTA); also elsewhere on the board
+3V3: C7.1, C8.1, L1.1, R6.1; also elsewhere on the board
+5V: C1.1, C2.1, C3.1, C13.1, U6.2 (VIN), U6.6 (EN), U7.2 (VIN), U8.2 (VCC), U8.3 (VCC), U8.11 (VCC); also elsewhere on the board
GND: C1.2, C2.2, C3.2, C4.2, C5.2, C7.2, C8.2, C9.2, C10.2, C11.2, C12.2, C13.2, R3.2, R5.2, R7.2, R9.2, R11.2, U6.5 (GND), U7.5 (GND), U8.4 (GND), U8.14 (PGND), U8.15 (PGND), U8.17 (PAD); also elsewhere on the board
unnamed: C4.1, U6.7 (BYP)
unnamed: C5.1, U7.7 (BYP)
unnamed: C6.1, L1.2, U8.1 (VSW), U8.12 (VSW), U8.13 (VSW), U8.16 (VSW)
unnamed: C6.2, U8.10 (BST)
unnamed: C9.1, R10.2, U7.1 (OUTB)
unnamed: R2.1, R3.1, U6.4 (FBA)
unnamed: R4.1, R5.1, U7.4 (FBA)
unnamed: R6.2, R7.1, U8.5 (FB)
unnamed: R8.1, R9.1, U6.8 (FBB)
unnamed: R10.1, R11.1, U7.8 (FBB)

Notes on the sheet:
3V3 [BOSON, SDMMC]
2V5 [FPGA Programming]
1V8 [FPGA + MCU]
1V2 [FPGA PLL]
Boson Max 520mA (during FFC)
Power up sequence. 1.2V -> 1.8V - >2.5V
EN has internal Pullup
Vout = 0.9 * ( 1 + (R_top/R_bot))
TS30011 1A DCDC supply
Vout = 1.0 * ( 1 + (R_top / R_bot))

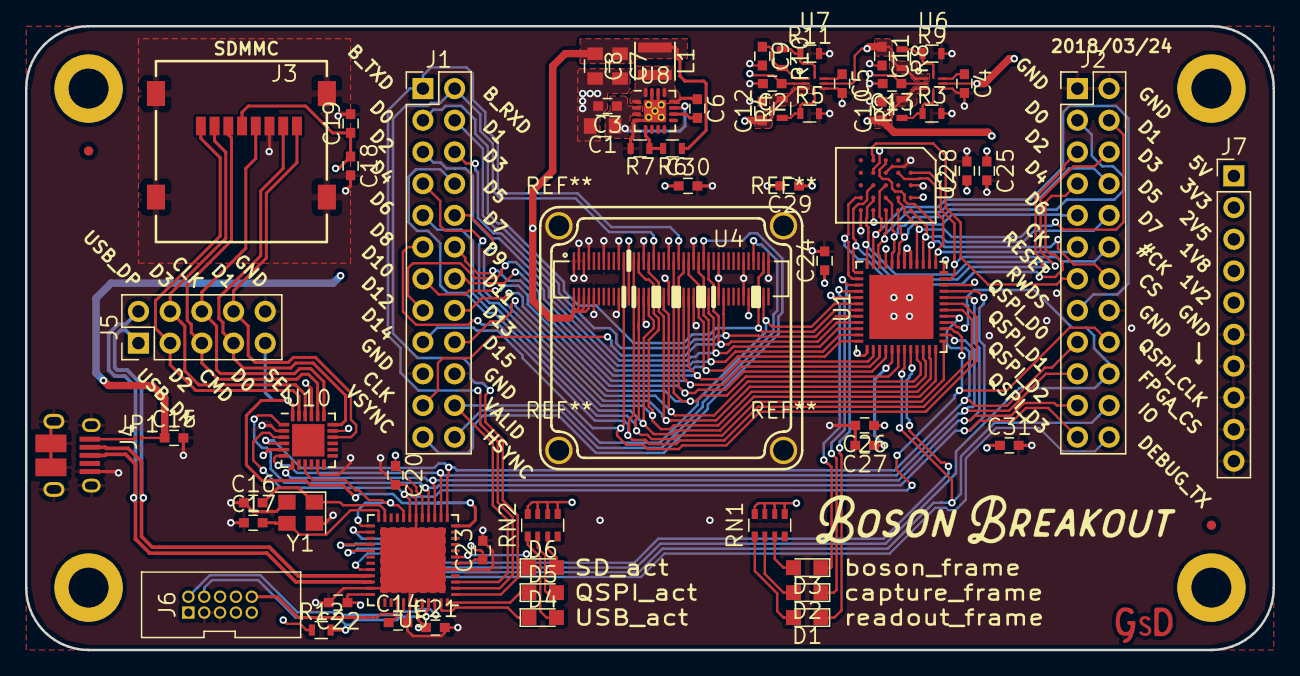
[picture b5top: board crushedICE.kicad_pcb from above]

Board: 4 copper layers, 100.0 x 50.0 mm, 68 parts (0 on the bottom side), 89 nets.
